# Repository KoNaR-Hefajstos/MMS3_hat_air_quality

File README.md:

# MMS3 Hat Air Quality

## Sekcja 1: Dokumentacja Hat'a

### Krótki opis projektu
Hat Air Quality to hat z miejscami na różne czujniki jakości powietrza. Są to 2x BME688 (lub kompatybilne) oraz po jednym PMS5003 (lub kompatybline), SCD40-D-R2, SGP41-D-R4, ENS160-BGLM oraz 4x miejsca na analogowe czujniki DFRobot (np. DFRobot SEN0564).

Dzięki temu potrafi mierzyć temperature, wilgotność, ciśnienie, VOC, IAQ, PM, CO2, NOX oraz wielkości mierzone przez 4x czujniki DFRobot

### Zgodność ze standardem ChainBus

* ✅ Używa złącza ChainBus, nie zmienia jego miejsca ani pinoutu.
* ✅ Używa wyłącznie interfejsów I2C, SPI lub UART i nie inicjuje samodzielnie nowych transmisji (Nie jest master'em I2C albo SPI).
* ✅ Spełnia wymagania mechaniczne standardu (wymiary PCB, rozstaw otworów).
* ❌ Pobiera maksymalny prąd zgodny z ilością na jednego hat'a **-> normalna praca >125mA, potrzeba określić empirycznie**
* ✅ Obsługuje napięcie wejściowe BRD_VIN do wartości 48V.

### Komunikacja i adresowanie

#### Adresacja I2C

| Układ (IC)      | Funkcja                   | Address |
| :-------------- | :------------------------ | :-----: |
| **BME688 #1**   | Czujnik jakości powietrza | `0x76`  |
| **BME688 #2**   | Czujnik jakości powietrza | `0x77`  |
| **SCD40-D-R2**  | Czujnik jakości powietrza | `0x62`  |
| **SGP41-D-R4**  | Czujnik jakości powietrza | `0x59`  |
| **ENS160-BGLM** | Czujnik jakości powietrza | `0x52`  |
| **ADS1115IDGS** | Przetwornik ADC           | `0x48`  |

#### Magistrala SPI
Brak urządzeń, ale CS może być użyty do włączania/wyłączania PMS5003

#### Magistrala UART
UART jest podłączony bezpośrednio do PMS5003.

| Układ (IC)  | Funkcja                   | chainbus/multiplexer |
| :---------- | :------------------------ | :------------------: |
| **PMS5003** | Czujnik jakości powietrza |      `chainbus`      |

### Pinout złączy

| Jn       | Co                | Jaki pin co robi                                                                                                                                                                                                                                                                                                                                                                                          |
| :------- | :---------------- | :-------------------------------------------------------------------------------------------------------------------------------------------------------------------------------------------------------------------------------------------------------------------------------------------------------------------------------------------------------------------------------------------------------- |
| **J101** | Złącze do PMS5003 | **Pin 1: +5V** <br>**Pin 2: GND**<br>**Pin 3: SET** – Wejście włączenia/uśpienia (Stan wysoki = normalna praca, Stan niski = tryb uśpienia)<br>**Pin 4: RX Czujnika**<br>**Pin 5: TX Czujnika** <br>**Pin 6: RST** – Reset modułu (aktywny stan niski - reset po podaniu GND)<br>**Pin 7: PWM** – Wyjście sygnału PWM, NC <br>**Pin 8: PROTOCOL** – Wybór protokołu/trybu pracy czujnika. Ma pulldown 10k |

### Konfiguracja układu (Zworki/Rezystory)

| Co                   | Jak podłączone        | Efekt                                  |
| :------------------- | :-------------------- | :------------------------------------- |
| **R101, R102, R104** | Wlutowany R104        | Pin SET zawsze wysoki                  |
|                      | Wlutowany  R101, R102 | Pin SET podłączony do pinu CS ChainBus |

### Szczegółowy opis techniczny
Czujniki BME688, SCD40-D-R2, SGP41-D-R4, ENS160-BGLM są bezpośrednio podłączone do magistrali I2C.

Czujniki analogowe DFRobot są podłączone do przetwornika ADC ADS1115IDGS. Kanały przetwornika 0-3 są podłączone do czujników 1-4.

 Czujnik PMS5003 jest bezpośrednio
podłączony do magistrali UART. Jego pin SEL domyślnie jest podciągany do +3.3V przez rezystor R104 (10k), ale można go wylutować
i wlutować R101 R102. Wtedy pin SEL jest bezpośrednio podłączony do pinu CS chainbus oraz ściągany (weak pulldown) do 0V przez R101 (10k).
Jeśli nie potrzebujesz oszczędzać prądu to zalecane jest zostawienie wlutowanego R104.

### Gotowe arkusze hierarchiczne
Brak

---

## Sekcja 2: Specyfikacja standardu ChainBus

### Architektura i łączenie modułów
Standard ChainBus umożliwia modułowe łączenie hatów. Na jednym MMS3 można zamontować pionowo **do 8 hat'ów**. Połączenie realizowane jest poprzez wpięcie złącza męskiego kolejnego hat'a w złącze żeńskie poprzedniego

### Komunikacja i sterowanie
Magistrala ChainBus jest w pełni cyfrowa. Płyta główna nie steruje bezpośrednio sygnałami ogólnego przeznaczenia (GPIO) na poszczególnych hat'ach. Wszelkie operacje (np. obsługa diod LED, odczyt krańcówek, generowanie sygnałów PWM) muszą być realizowane przez dedykowane układy scalone (np. ekspandery portów, sterowniki) komunikujące się przez interfejsy systemowe.

*Przykład:*
`MCU` $\rightarrow$ `Expander GPIO po I2C` $\rightarrow$ `Dioda LED`

Wybór aktywnego modułu realizowany jest przez układ przełącznika magistrali (bus switch) na płycie głównej. Dzięki temu linie I2C, SPI i UART są niezależne dla każdego hat'a (brak konfliktów adresów I2C między różnymi hatami).
* **Identyfikacja:** Każdy moduł powinien posiadać pamięć EEPROM na magistrali I2C w celu identyfikacji płyty przez system - układ M24C64-W skonfigurowany na adres `1010000` przy liniach adresowych A0, A1, A2 zwartych do masy.

### Zasilanie
Złącze ChainBus dostarcza następujące linie zasilania:

| Magistrala zasilania | Napięcie znamionowe | Maksymalny prąd (łączny dla 8 hatów) | Szacowany prąd na jeden hat |
| :------------------- | :-----------------: | :----------------------------------: | :-------------------------: |
| **5V**               |        5.0 V        |                1.0 A                 |           125 mA            |
| **12V stby**         |       12.0 V        |                0.5 A                 |            65 mA            |
| **BRD_VIN**          |   12.0 V – 48.0 V   |                1.5 A                 |           185 mA            |

*   Komponenty podłączone do linii `BRD_VIN` muszą być przystosowane do pracy z napięciem od 12V do **48 V**.
*   W przypadku zapotrzebowania na wyższą moc, dopuszczalne jest zastosowanie dodatkowego złącza zasilania XT60 (obciążalność do ok. 60 A).

### Wymagania mechaniczne i złącza
* **Wymiary PCB:** Niedozwolona jest zmiana obrysu płytki oraz położenia otworów montażowych, aby zachować kompatybilność mechaniczną.
* **Pozycjonowanie złączy ChainBus:** Położenie złącza standardu 2x16 SMD (raster 2.54 mm) musi być zgodne z szablonem. Złącze żeńskie montowane jest na stronie FRONT, natomiast złącze męskie na stronie BACK.
* **Interfejsy zewnętrzne:** Złącza wejścia/wyjścia (domyślnie standard JST-XH 2.5 mm o obciążalności do 3 A) oraz opcjonalne złącze XT60 powinny być umieszczone przy dolnej krawędzi płytki. Elementy regulacyjne i sygnalizacyjne (potencjometry, przełączniki, diody LED) należy lokalizować przy prawej krawędzi płytki.
* **Komponenty** Wszystkie komponenty powinny być na stronie front płytki żeby nie haczyły o elementy ze wcześniejszego hat'a

---

## Sekcja 3: Licencja, linki i tagi

### Licencjonowanie projektu

*   **PCB:** CERN-OHL-P
*   **Software:** MIT License

[Template](https://github.com/KoNaR-Hefajstos/MMS3_hat_templates/) jest na licencji CC0 1.0 Universal. **Reszta projektu nie jest na tej licencji**

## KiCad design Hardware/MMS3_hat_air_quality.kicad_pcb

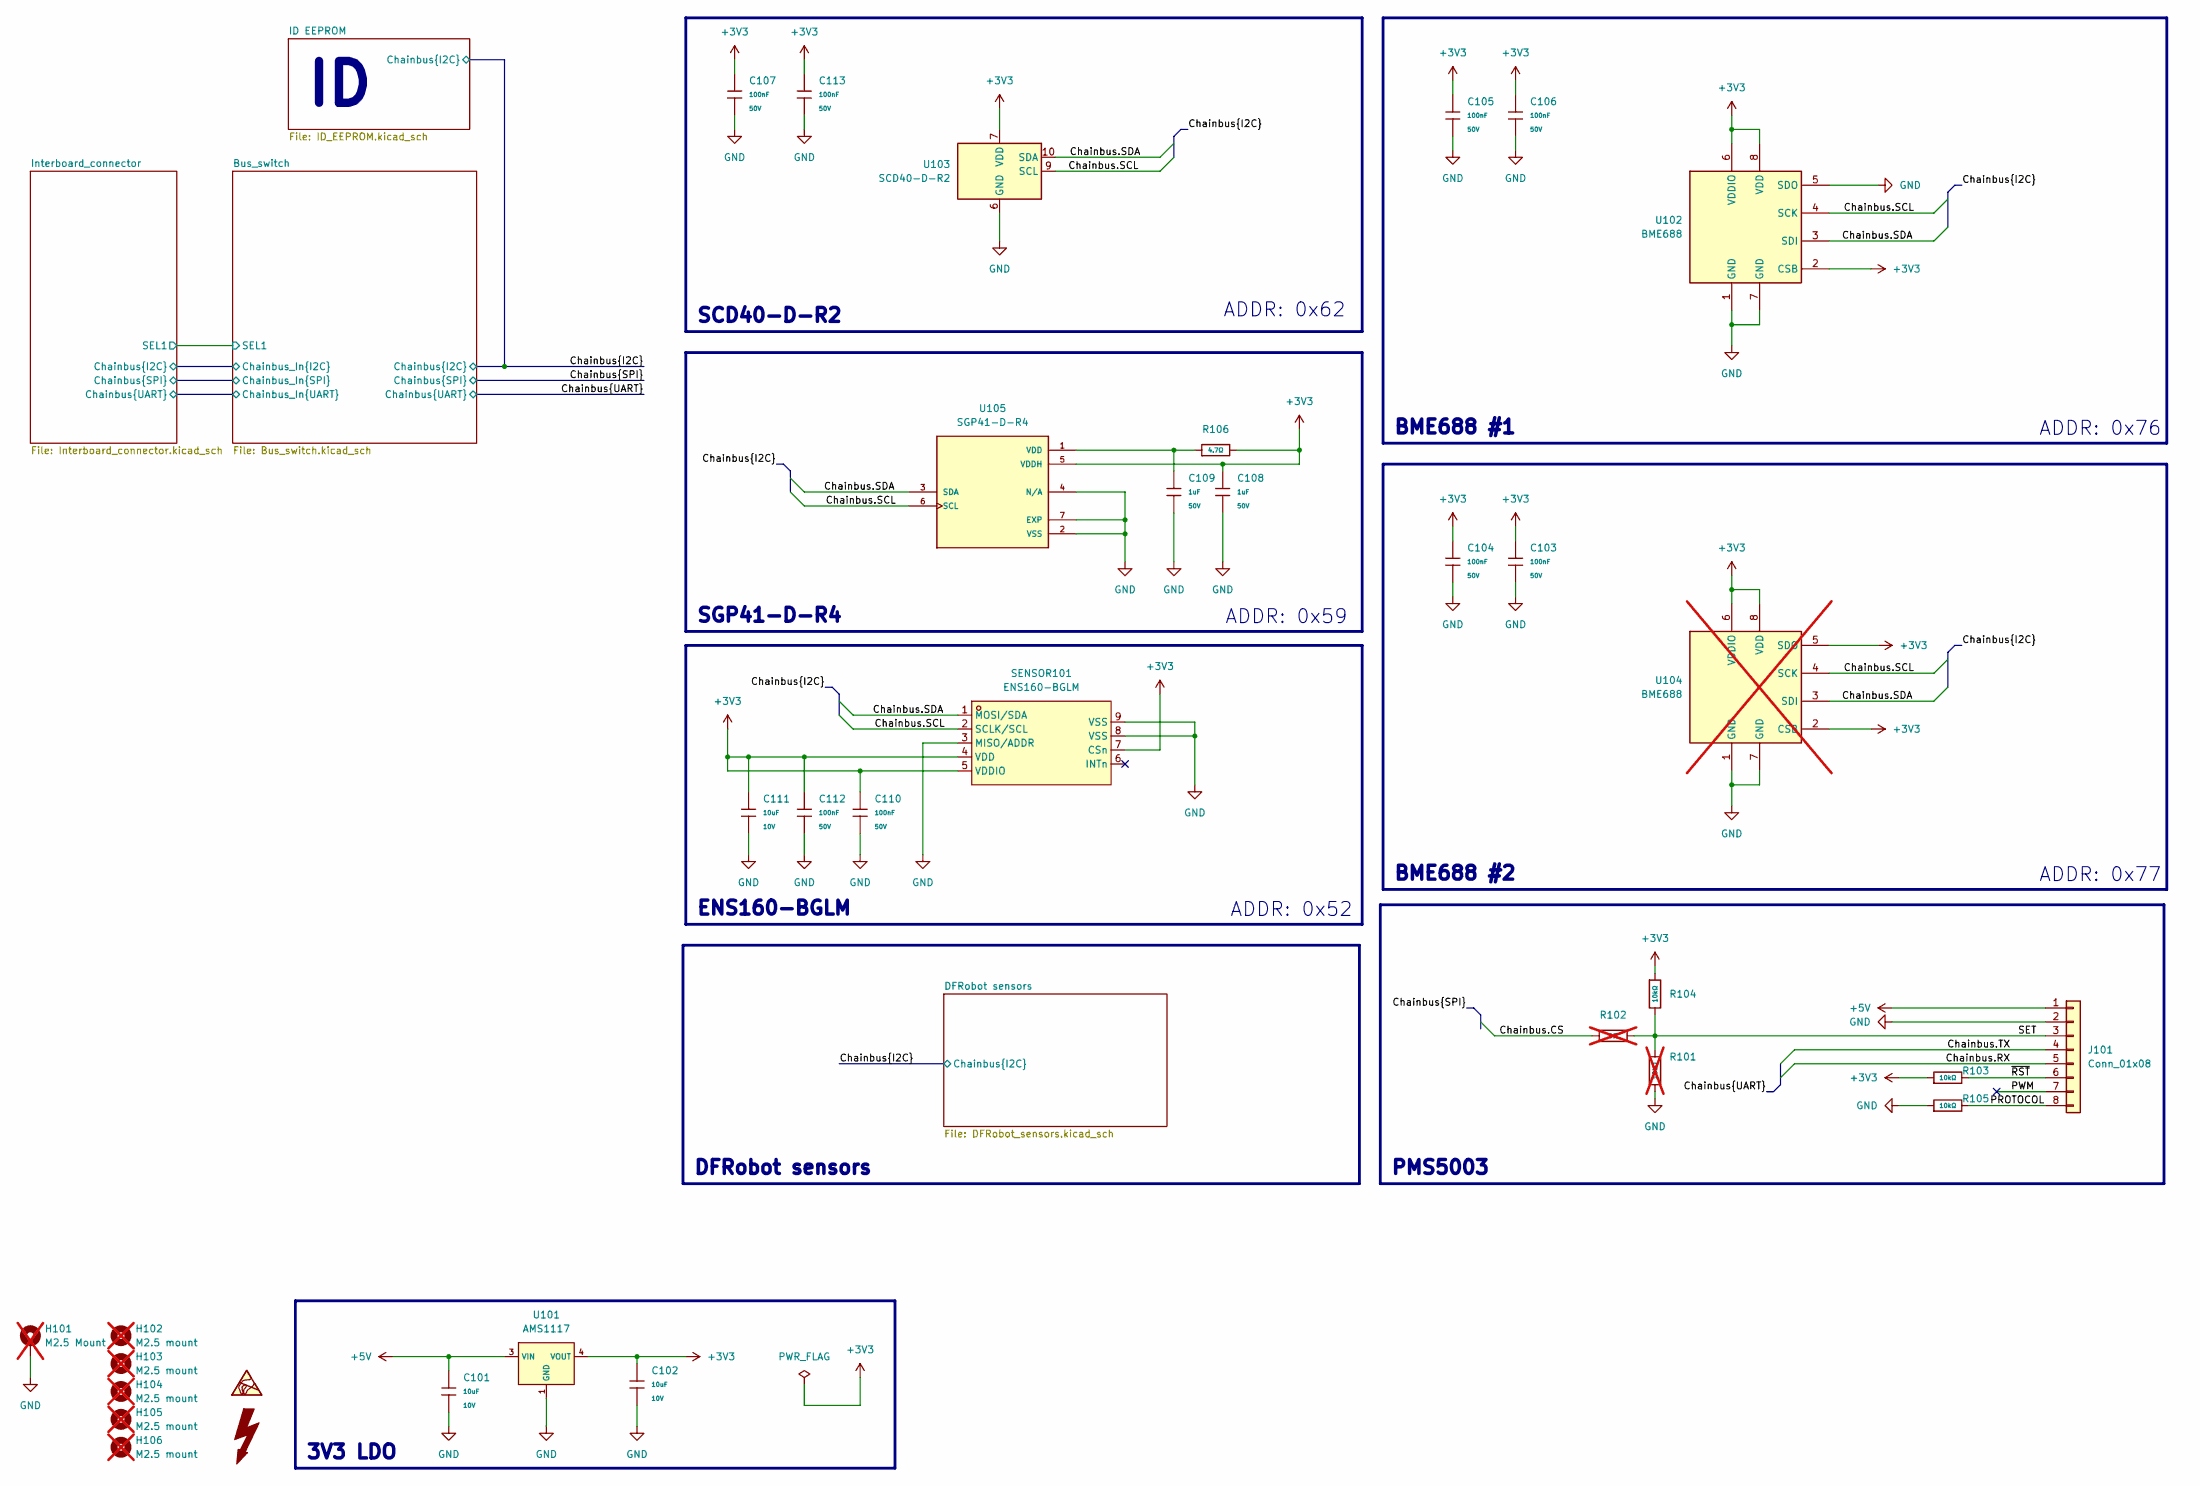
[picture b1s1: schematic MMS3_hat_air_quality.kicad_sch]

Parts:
C101, C102, C111: 10uF; C_0603; Voltage Rated 10V; Tolerance ±10%; Part CL10A106KP8NNNC; LCSC C19702
C103, C104, C105, C106, C107, C110, C112, C113: 100nF; C_0603; Voltage Rated 50V; Tolerance ±10%; Part CC0603KRX7R9BB104; LCSC C14663
C108, C109: 1uF; C_0603; Voltage Rated 50V; Tolerance ±10%; Part CL10A105KB8NNNC; LCSC C15849
H101: M2.5 Mount; MountingHole_2.7mm_M2.5_DIN965_Pad_TopOnly; not fitted
H102, H103, H104, H105, H106: M2.5 mount; MountingHole_2.7mm_M2.5; not fitted
J101: Conn_01x08; JST_XH_S8B-XH-A-1_1x08_P2.50mm_Horizontal
R101: 10kΩ; R_0603; Overload Voltage (Max) 75V; Tolerance ±1%; Part 0603WAF1002T5E; LCSC C25804; not fitted
R102: 0Ω; R_0603; Overload Voltage (Max) 75V; Tolerance ±1%; Part 0603WAF0000T5E; LCSC C21189; not fitted
R103, R104, R105: 10kΩ; R_0603; Overload Voltage (Max) 75V; Tolerance ±1%; Part 0603WAF1002T5E; LCSC C25804
R106: 4.7Ω; R_0603; Overload Voltage (Max) 75V; Tolerance ±1%; Part 0603WAF470KT5E; LCSC C23164
SENSOR101: ENS160-BGLM; SENSOR-SMD_ENS160-BGLM; MPN ENS160-BGLM; LCSC Part C3659288
U101: AMS1117; SOT-223-3_L6.5-W3.4-P2.30-LS7.0-BR; Output Voltage 3.3V; Dropout Voltage 1.3V@(800mA); Part AMS1117-3.3; LCSC C6186
U102: BME688; Bosch_LGA-8_3x3mm_P0.8mm_ClockwisePinNumbering
U103: SCD40-D-R2; Sensirion_SCD4x-1EP_10.1x10.1mm_P1.25mm_EP4.8x4.8mm; LCSC C3659421
U104: BME688; Bosch_LGA-8_3x3mm_P0.8mm_ClockwisePinNumbering; not fitted
U105: SGP41-D-R4; XDCR_SGP41-D-R4; PARTREV 1.0

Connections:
+3V3: C102.1, C103.1, C104.1, C105.1, C106.1, C107.1, C108.1, C110.1, C111.1, C112.1, C113.1, R103.1, R104.1, R106.2, SENSOR101.4 (VDD), SENSOR101.5 (VDDIO), SENSOR101.7 (CSn), U101.2 (VOUT), U101.4 (VOUT), U102.2 (CSB), U102.6 (VDDIO), U102.8 (VDD), U103.7 (VDD), U103.19 (VDD), U104.2 (CSB), U104.5 (SDO), U104.6 (VDDIO), U104.8 (VDD), U105.5 (VDDH); also elsewhere on the board
+5V: C101.1, J101.1, U101.3 (VIN); also elsewhere on the board
/Chainbus.CS: R102.1; also elsewhere on the board
/Chainbus.RX: J101.5; also elsewhere on the board
/Chainbus.SCL: SENSOR101.2 (SCLK/SCL), U102.4 (SCK), U103.9 (SCL), U104.4 (SCK), U105.6 (SCL); also elsewhere on the board
/Chainbus.SDA: SENSOR101.1 (MOSI/SDA), U102.3 (SDI), U103.10 (SDA), U104.3 (SDI), U105.3 (SDA); also elsewhere on the board
/Chainbus.TX: J101.4; also elsewhere on the board
/PROTOCOL: J101.8, R105.2
/PWM: J101.7
/SET: J101.3, R101.1, R102.2, R104.2
/~RST: J101.6, R103.2
GND: C101.2, C102.2, C103.2, C104.2, C105.2, C106.2, C107.2, C108.2, C109.2, C110.2, C111.2, C112.2, C113.2, H101.1 (1_1), J101.2, R101.2, R105.1, SENSOR101.3 (MISO/ADDR), SENSOR101.8 (VSS), SENSOR101.9 (VSS), U101.1 (GND), U102.1 (GND), U102.5 (SDO), U102.7 (GND), U103.6 (GND), U103.20 (GND), U103.21 (GND), U104.1 (GND), U104.7 (GND), U105.2 (VSS), U105.4 (N/A), U105.7 (EXP); also elsewhere on the board
unnamed: C109.1, R106.1, U105.1 (VDD)

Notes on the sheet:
ADDR: 0x59
BME688 #2
SGP41-D-R4
ADDR: 0x77
PMS5003
ADDR: 0x62
ADDR: 0x52
DFRobot sensors
SCD40-D-R2
ADDR: 0x76
3V3 LDO
BME688 #1
ENS160-BGLM

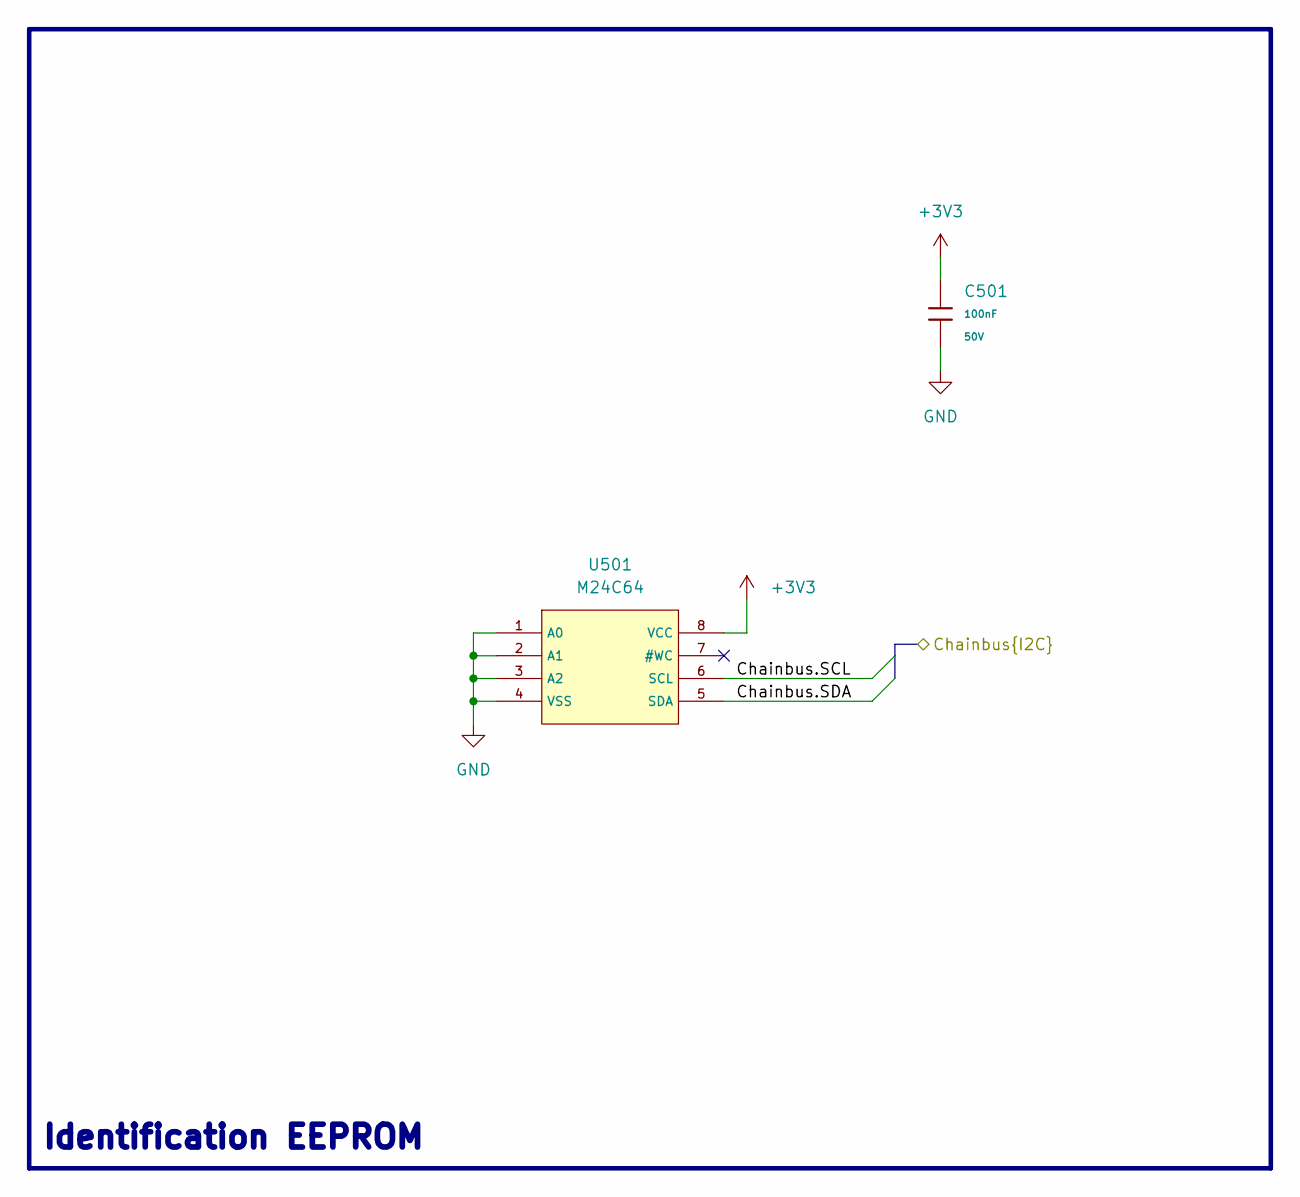
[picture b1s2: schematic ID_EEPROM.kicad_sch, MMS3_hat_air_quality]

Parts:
C501: 100nF; C_0603; Voltage Rated 50V; Tolerance ±10%; Part CC0603KRX7R9BB104; LCSC C14663
U501: M24C64; SOIC-8_L5.0-W4.0-P1.27-LS6.0-BL; Supply Voltage 1.8V~5.5V; Part M24C64-RMN6TP; LCSC C79988

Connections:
+3V3: C501.1, U501.8 (VCC); also elsewhere on the board
/Chainbus.SCL: U501.6 (SCL); also elsewhere on the board
/Chainbus.SDA: U501.5 (SDA); also elsewhere on the board
GND: C501.2, U501.1 (A0), U501.2 (A1), U501.3 (A2), U501.4 (VSS); also elsewhere on the board

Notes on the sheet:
Identification EEPROM

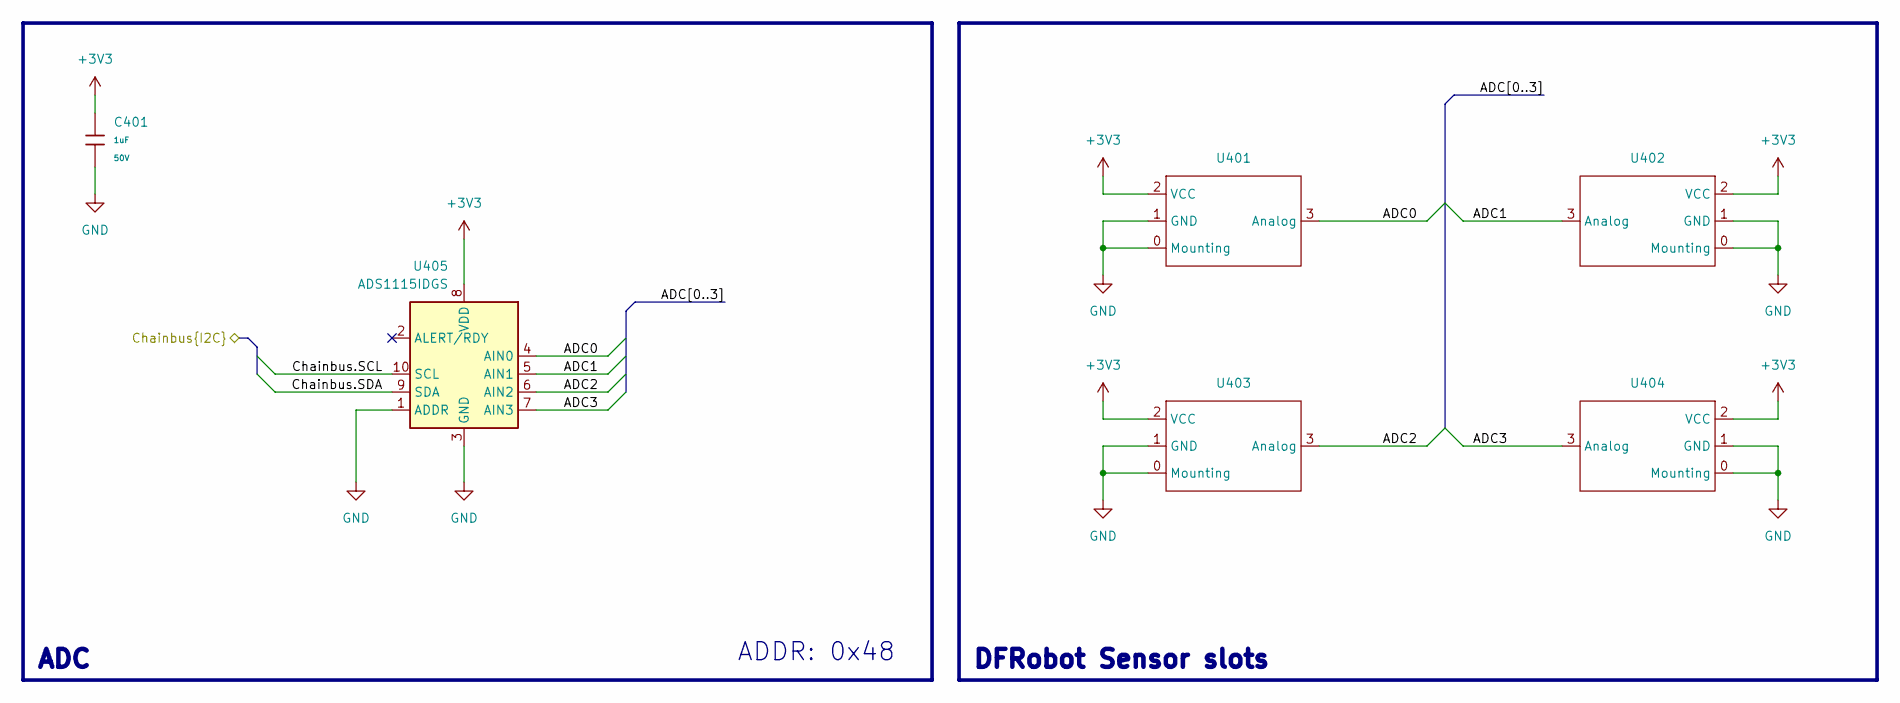
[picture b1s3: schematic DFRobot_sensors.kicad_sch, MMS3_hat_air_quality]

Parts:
C401: 1uF; C_0603; Voltage Rated 50V; Tolerance ±10%; Part CL10A105KB8NNNC; LCSC C15849
U401, U402, U403, U404: DFRobot
U405: ADS1115IDGS; TSSOP-10_3x3mm_P0.5mm; LCSC C37593

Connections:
+3V3: C401.1, U401.2 (VCC), U402.2 (VCC), U403.2 (VCC), U404.2 (VCC), U405.8 (VDD); also elsewhere on the board
/Chainbus.SCL: U405.10 (SCL); also elsewhere on the board
/Chainbus.SDA: U405.9 (SDA); also elsewhere on the board
/DFRobot sensors/ADC0: U401.3 (Analog), U405.4 (AIN0)
/DFRobot sensors/ADC1: U402.3 (Analog), U405.5 (AIN1)
/DFRobot sensors/ADC2: U403.3 (Analog), U405.6 (AIN2)
/DFRobot sensors/ADC3: U404.3 (Analog), U405.7 (AIN3)
GND: C401.2, U401.0 (Mounting), U401.1 (GND), U402.0 (Mounting), U402.1 (GND), U403.0 (Mounting), U403.1 (GND), U404.0 (Mounting), U404.1 (GND), U405.1 (ADDR), U405.3 (GND); also elsewhere on the board

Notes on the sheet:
ADC
ADDR: 0x48
DFRobot Sensor slots

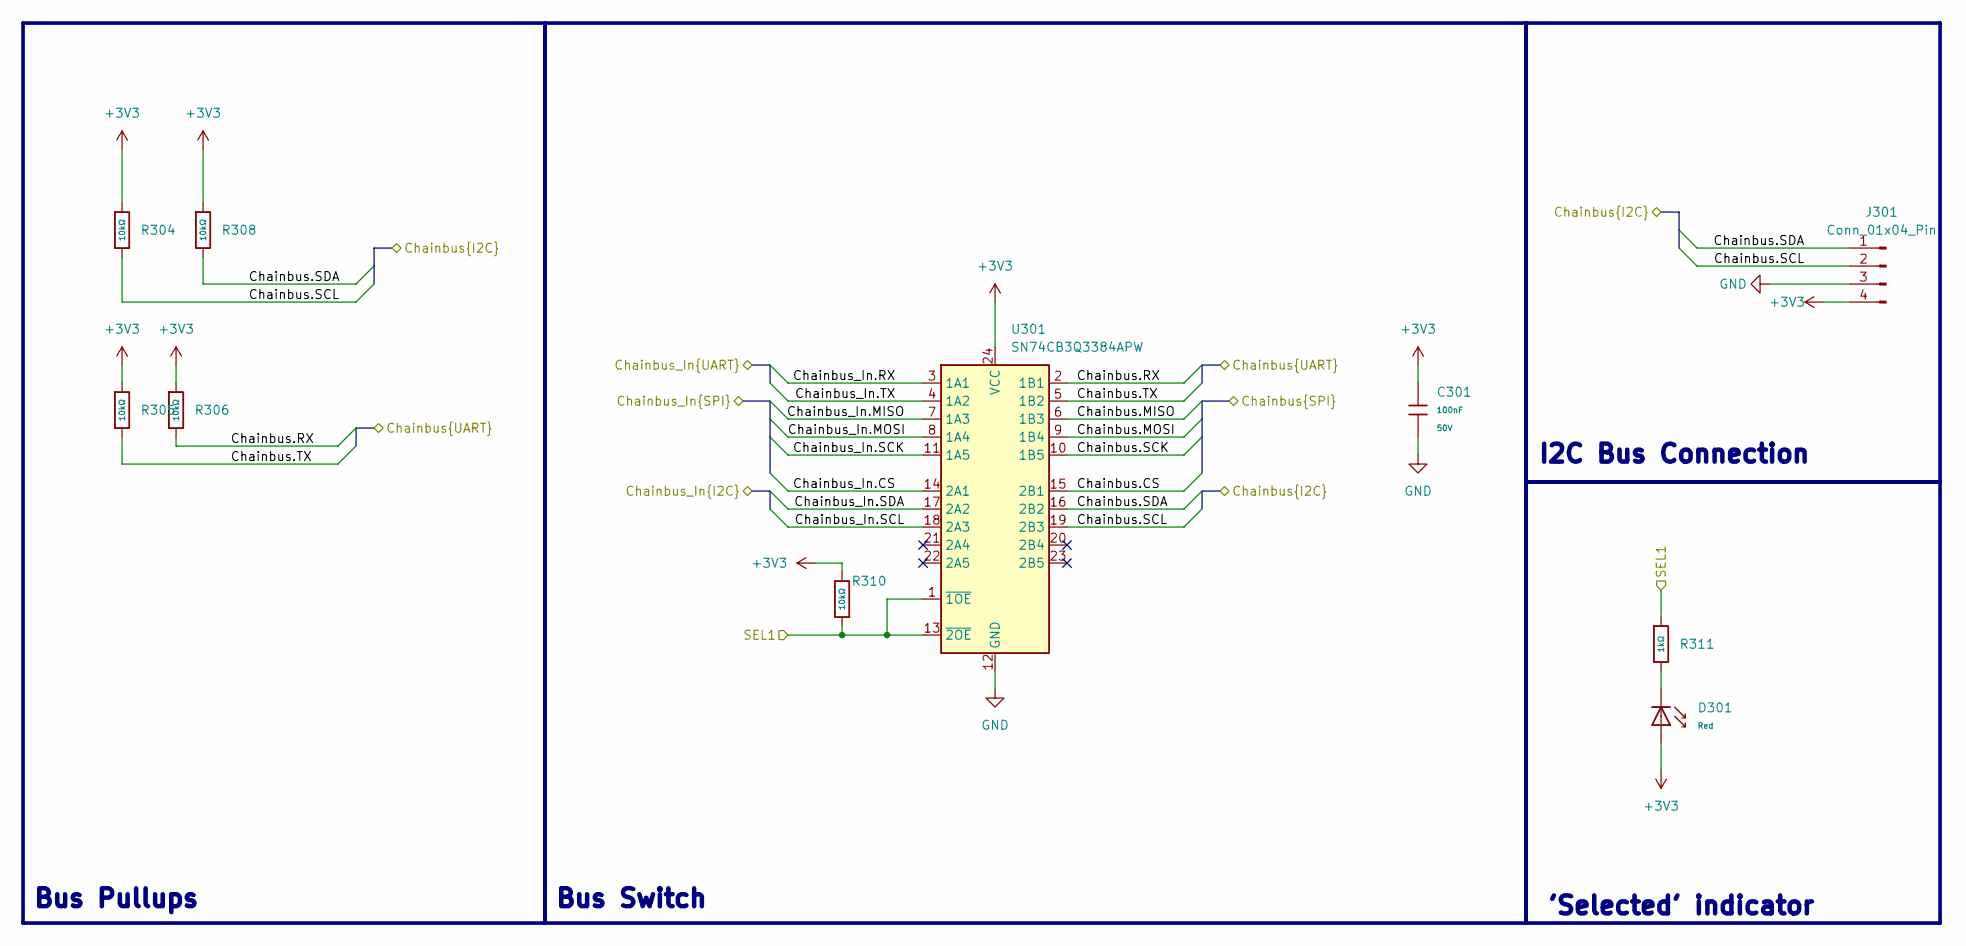
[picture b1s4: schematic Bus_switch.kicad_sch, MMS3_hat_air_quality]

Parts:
C301: 100nF; C_0603; Voltage Rated 50V; Tolerance ±10%; Part CC0603KRX7R9BB104; LCSC C14663
D301: Red; D_0603; Part KT-0603R; LCSC C2286
J301: Conn_01x04_Pin; PinHeader_1x04_P2.54mm_Vertical
R304, R305, R306, R308, R310: 10kΩ; R_0603; Overload Voltage (Max) 75V; Tolerance ±1%; Part 0603WAF1002T5E; LCSC C25804
R311: 1kΩ; R_0603; Overload Voltage (Max) 75V; Tolerance ±1%; Part 0603WAF1001T5E; LCSC C21190
U301: SN74CB3Q3384APW; TSSOP-24_4.4x7.8mm_P0.65mm; LCSC C469874

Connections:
+3V3: C301.1, D301.2, J301.4, R304.1, R305.1, R306.1, R308.1, R310.1, U301.24 (VCC); also elsewhere on the board
/Bus_switch/Chainbus_In.CS: U301.14 (2A1); also elsewhere on the board
/Bus_switch/Chainbus_In.MISO: U301.7 (1A3); also elsewhere on the board
/Bus_switch/Chainbus_In.MOSI: U301.8 (1A4); also elsewhere on the board
/Bus_switch/Chainbus_In.RX: U301.3 (1A1); also elsewhere on the board
/Bus_switch/Chainbus_In.SCK: U301.11 (1A5); also elsewhere on the board
/Bus_switch/Chainbus_In.SCL: U301.18 (2A3); also elsewhere on the board
/Bus_switch/Chainbus_In.SDA: U301.17 (2A2); also elsewhere on the board
/Bus_switch/Chainbus_In.TX: U301.4 (1A2); also elsewhere on the board
/Bus_switch/SEL1: R310.2, R311.1, U301.1 (~1OE), U301.13 (~2OE); also elsewhere on the board
/Chainbus.CS: U301.15 (2B1); also elsewhere on the board
/Chainbus.MISO: U301.6 (1B3)
/Chainbus.MOSI: U301.9 (1B4)
/Chainbus.RX: R306.2, U301.2 (1B1); also elsewhere on the board
/Chainbus.SCK: U301.10 (1B5)
/Chainbus.SCL: J301.2, R304.2, U301.19 (2B3); also elsewhere on the board
/Chainbus.SDA: J301.1, R308.2, U301.16 (2B2); also elsewhere on the board
/Chainbus.TX: R305.2, U301.5 (1B2); also elsewhere on the board
GND: C301.2, J301.3, U301.12 (GND); also elsewhere on the board
unnamed: D301.1, R311.2

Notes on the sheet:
Bus Switch
'Selected' indicator
Bus Pullups
I2C Bus Connection

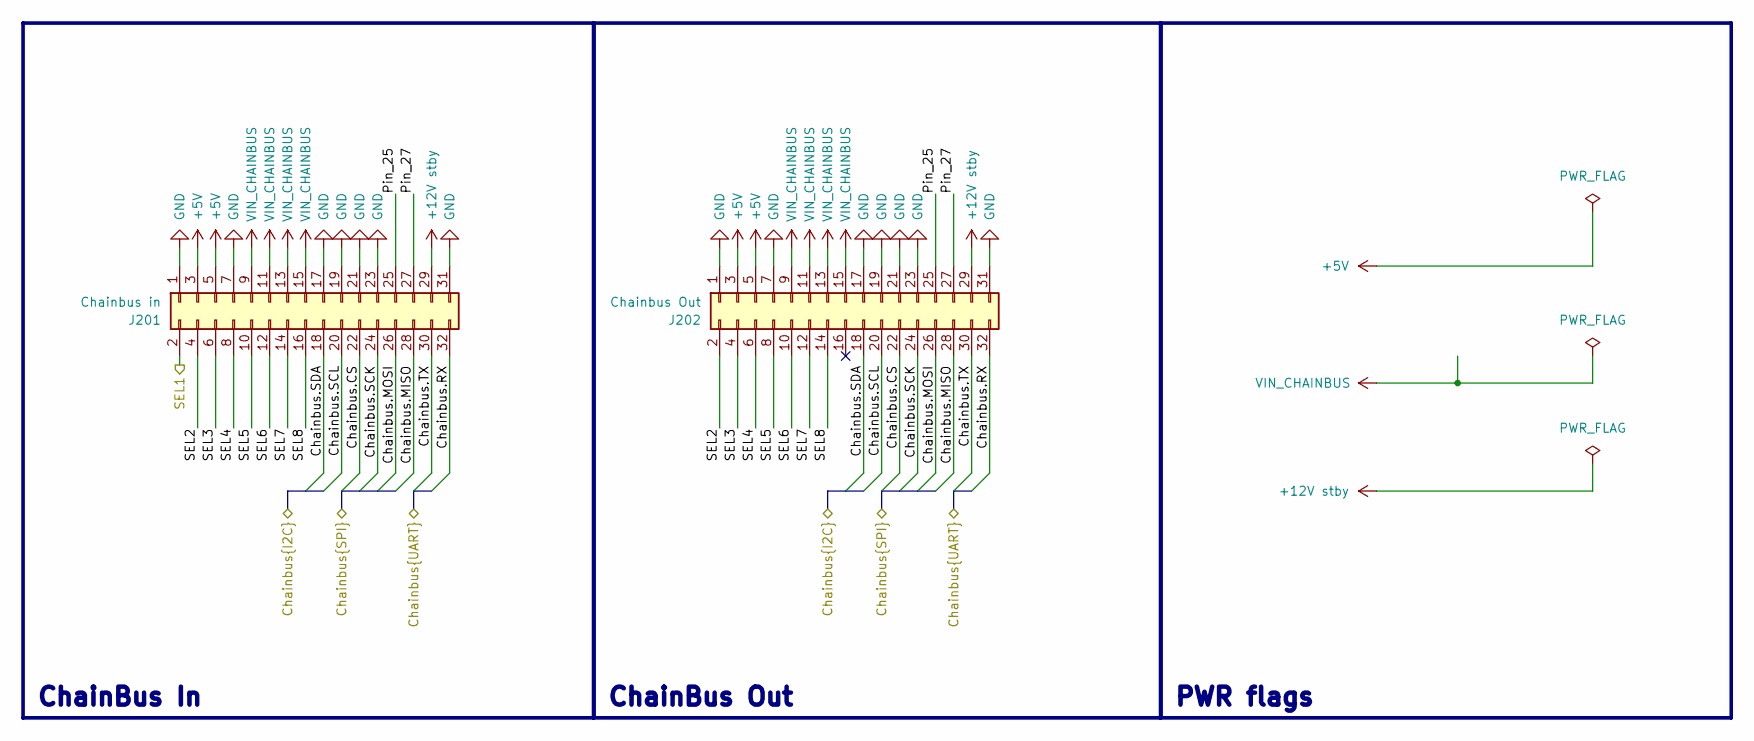
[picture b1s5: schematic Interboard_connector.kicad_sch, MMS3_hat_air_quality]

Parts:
J201: Chainbus in; PinHeader_2x16_P2.54mm_Vertical_SMD
J202: Chainbus Out; PinSocket_2x16_P2.54mm_Vertical_SMD

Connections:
+5V: J201.3, J201.5, J202.3, J202.5; also elsewhere on the board
+12V stby: J201.29, J202.29
/Bus_switch/Chainbus_In.CS: J201.22, J202.22; also elsewhere on the board
/Bus_switch/Chainbus_In.MISO: J201.28, J202.28; also elsewhere on the board
/Bus_switch/Chainbus_In.MOSI: J201.26, J202.26; also elsewhere on the board
/Bus_switch/Chainbus_In.RX: J201.32, J202.32; also elsewhere on the board
/Bus_switch/Chainbus_In.SCK: J201.24, J202.24; also elsewhere on the board
/Bus_switch/Chainbus_In.SCL: J201.20, J202.20; also elsewhere on the board
/Bus_switch/Chainbus_In.SDA: J201.18, J202.18; also elsewhere on the board
/Bus_switch/Chainbus_In.TX: J201.30, J202.30; also elsewhere on the board
/Bus_switch/SEL1: J201.2; also elsewhere on the board
/Interboard_connector/Pin_25: J201.25, J202.25
/Interboard_connector/Pin_27: J201.27, J202.27
/Interboard_connector/SEL2: J201.4, J202.2
/Interboard_connector/SEL3: J201.6, J202.4
/Interboard_connector/SEL4: J201.8, J202.6
/Interboard_connector/SEL5: J201.10, J202.8
/Interboard_connector/SEL6: J201.12, J202.10
/Interboard_connector/SEL7: J201.14, J202.12
/Interboard_connector/SEL8: J201.16, J202.14
GND: J201.1, J201.7, J201.17, J201.19, J201.21, J201.23, J201.31, J202.1, J202.7, J202.17, J202.19, J202.21, J202.23, J202.31; also elsewhere on the board
VIN_CHAINBUS: J201.9, J201.11, J201.13, J201.15, J202.9, J202.11, J202.13, J202.15

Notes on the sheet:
ChainBus In
PWR flags
ChainBus Out

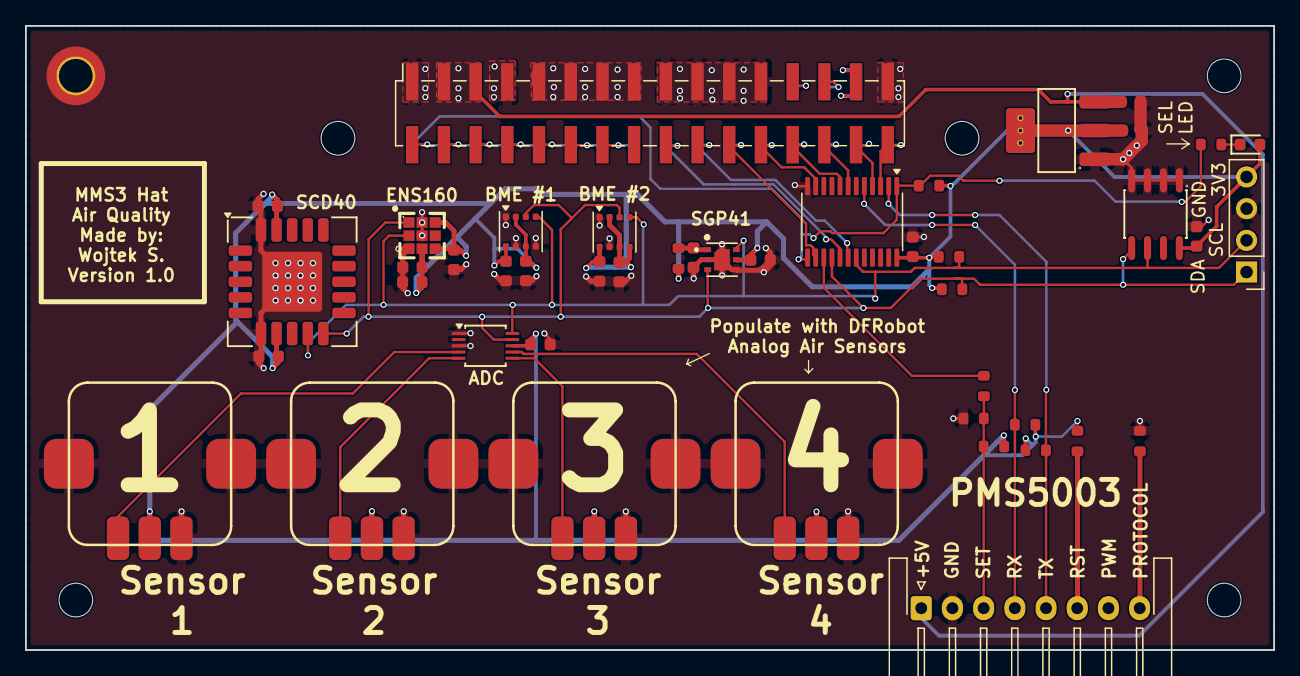
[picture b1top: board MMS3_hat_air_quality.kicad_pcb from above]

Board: 2 copper layers, 100.0 x 50.0 mm, 52 parts (1 on the bottom side), 37 nets.
